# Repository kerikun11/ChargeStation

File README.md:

# ChargeStation
PICで作った携帯電話の充電器

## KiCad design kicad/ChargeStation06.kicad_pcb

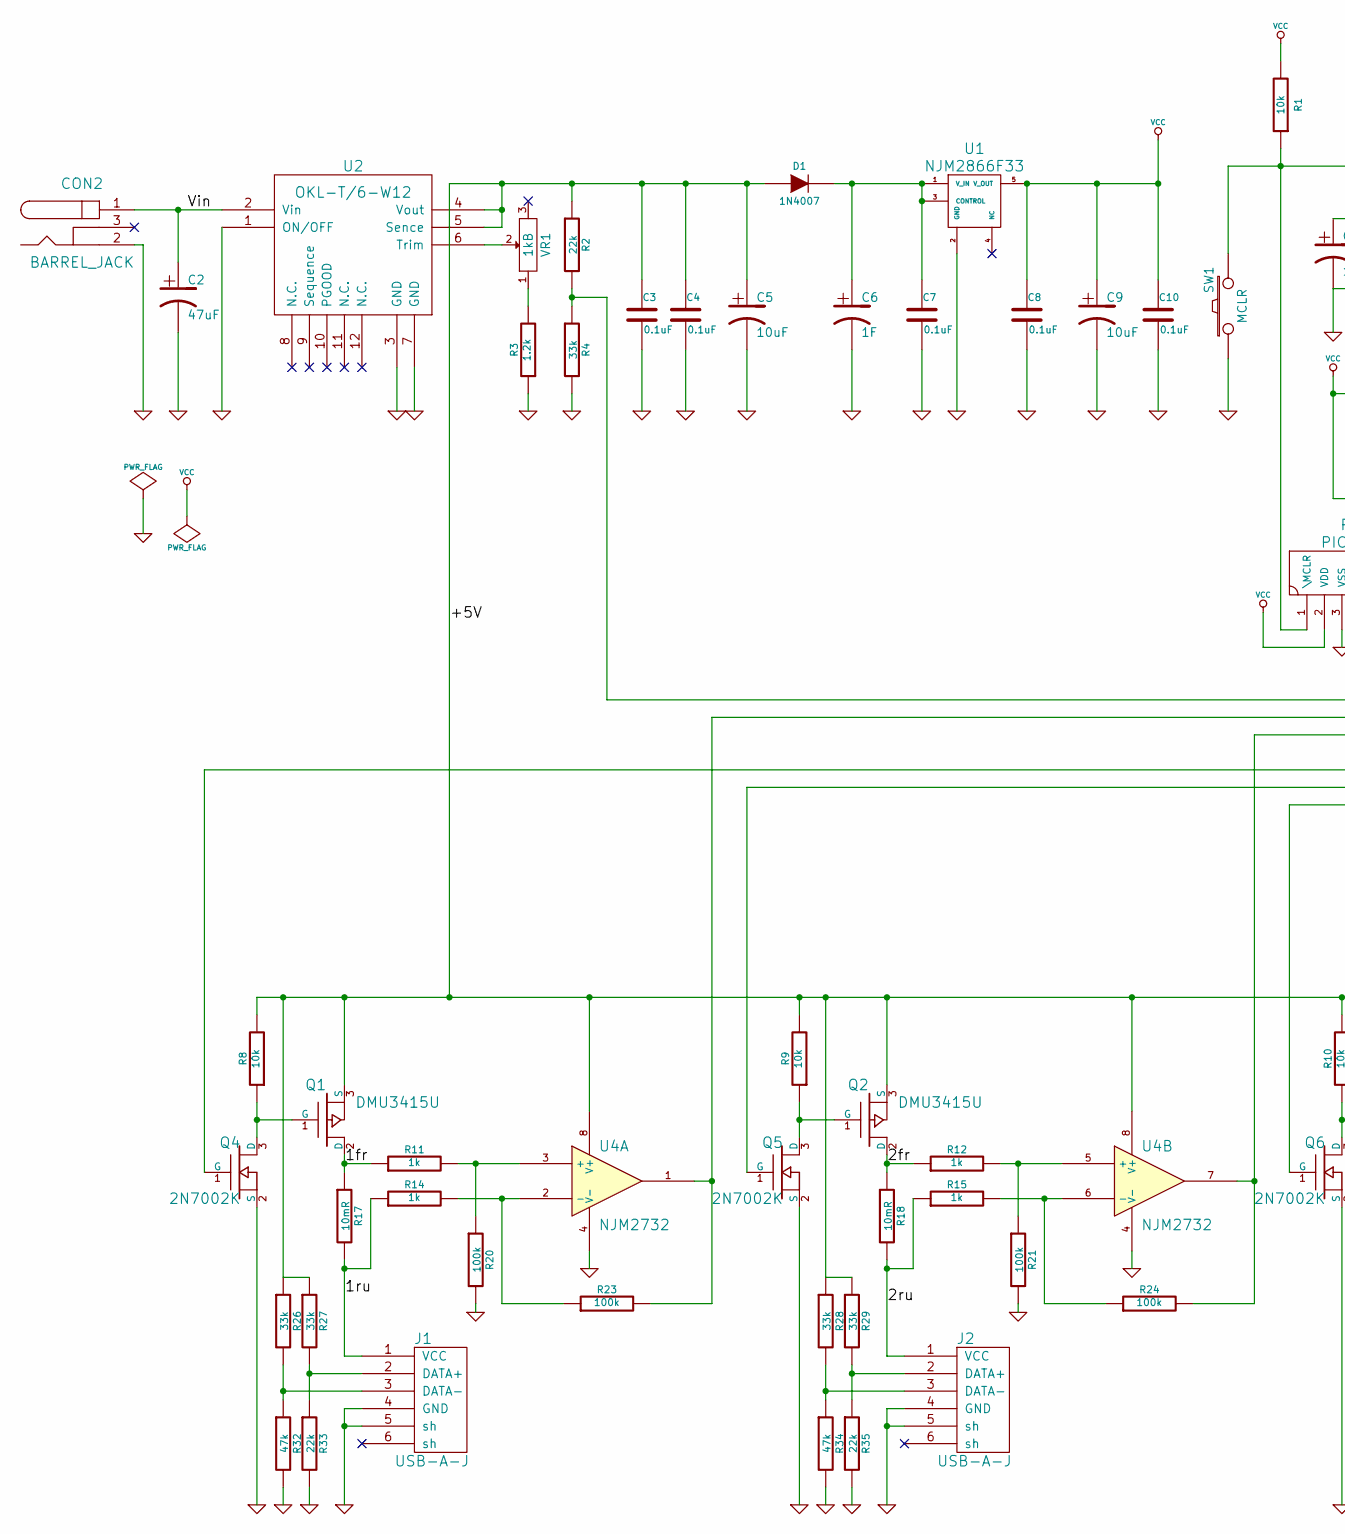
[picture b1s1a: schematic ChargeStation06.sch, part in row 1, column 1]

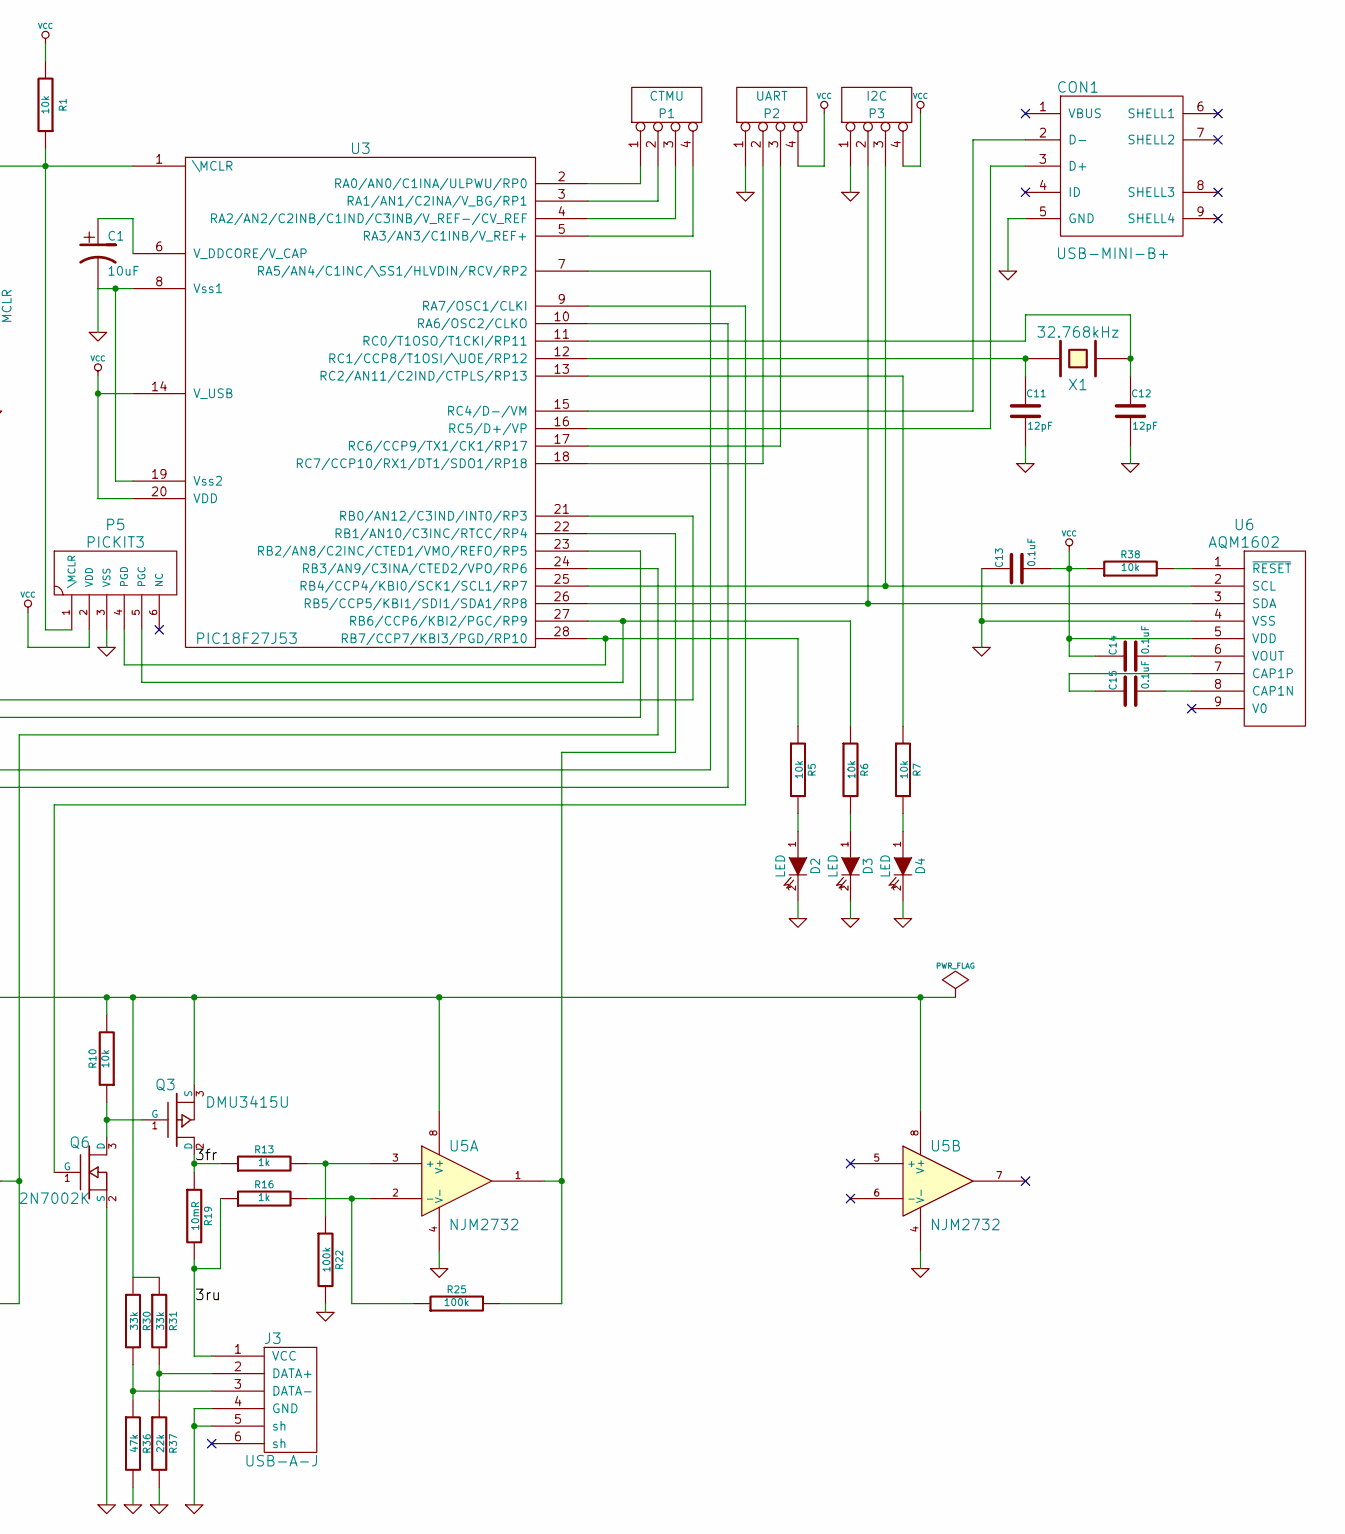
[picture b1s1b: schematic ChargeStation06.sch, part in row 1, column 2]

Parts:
C1, C5, C9: 10uF
C2: 47uF
C3, C4, C7, C8, C10, C13, C14, C15: 0.1uF
C6: 1F
C11, C12: 12pF
CON1: USB-MINI-B+
CON2: BARREL_JACK
D1: 1N4007
D2, D3, D4: LED
J1, J2, J3: USB-A-J
P1: CTMU
P2: UART
P3: I2C
P5: PICKIT3
Q1, Q2, Q3: DMU3415U
Q4, Q5, Q6: 2N7002K
R1, R5, R6, R7, R8, R9, R10, R38: 10k
R2, R33, R35, R37: 22k
R3: 1.2k
R4, R26, R27, R28, R29, R30, R31: 33k
R11, R12, R13, R14, R15, R16: 1k
R17, R18, R19: 10mR
R20, R21, R22, R23, R24, R25: 100k
R32, R34, R36: 47k
SW1: MCLR
U1: NJM2866F33
U2: OKL-T/6-W12
U3: PIC18F27J53
U4, U5: NJM2732
U6: AQM1602
VR1: 1kB
X1: 32.768kHz

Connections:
/1fr: Q1.2 (D), R11.1, R17.1
/1ru: J1.1 (VCC), R14.1, R17.2
/2fr: Q2.2 (D), R12.1, R18.1
/2ru: J2.1 (VCC), R15.1, R18.2
/3fr: Q3.2 (D), R13.1, R19.1
/3ru: J3.1 (VCC), R16.1, R19.2
/+5V: C3.1, C4.1, C5.1, D1.1 (A), Q1.3 (S), Q2.3 (S), Q3.3 (S), R2.1, R8.2, R9.2, R10.2, R26.1, R27.1, R28.1, R29.1, R30.1, R31.1, U2.4 (Vout), U2.5 (Sence), U4.8 (V+), U5.8 (V+)
/Vin: C2.1, CON2.1, U2.2 (Vin)
GND: C1.2, C2.2, C3.2, C4.2, C5.2, C6.2, C7.2, C8.2, C9.2, C10.2, C11.2, C12.2, C13.1, CON1.5 (GND), CON2.2, D2.2 (K), D3.2 (K), D4.2 (K), J1.4 (GND), J1.5 (sh), J2.4 (GND), J2.5 (sh), J3.4 (GND), J3.5 (sh), P2.1, P3.1, P5.3 (VSS), Q4.2 (S), Q5.2 (S), Q6.2 (S), R3.1, R4.2, R20.2, R21.2, R22.2, R32.2, R33.2, R34.2, R35.2, R36.2, R37.2, SW1.1, U1.2 (GND), U2.1 (ON/OFF), U2.3 (GND), U2.7 (GND), U3.8 (Vss1), U3.19 (Vss2), U4.4 (V-), U5.4 (V-), U6.4 (VSS)
unnamed: J3.3 (DATA-), R30.2, R36.1
unnamed: J3.2 (DATA+), R31.2, R37.1
unnamed: R13.2, R22.1, U5.3 (+)
unnamed: Q2.1 (G), Q5.3 (D), R9.1
unnamed: R24.2, U3.24 (RB3/AN9/C3INA/CTED2/VPO/RP6), U4.7
unnamed: R15.2, R24.1, U4.6 (-)
unnamed: Q3.1 (G), Q6.3 (D), R10.1
unnamed: R25.2, U3.22 (RB1/AN10/C3INC/RTCC/RP4), U5.1
unnamed: R16.2, R25.1, U5.2 (-)
unnamed: Q1.1 (G), Q4.3 (D), R8.1
unnamed: R23.2, U3.23 (RB2/AN8/C2INC/CTED1/VMO/REFO/RP5), U4.1
unnamed: R14.2, R23.1, U4.2 (-)
unnamed: R2.2, R4.1, U3.21 (RB0/AN12/C3IND/INT0/RP3)
unnamed: J2.3 (DATA-), R28.2, R34.1
unnamed: J2.2 (DATA+), R29.2, R35.1
unnamed: R12.2, R21.1, U4.5 (+)
unnamed: Q6.1 (G), U3.9 (RA7/OSC1/CLKI)
unnamed: CON1.2 (D-), U3.15 (RC4/D-/VM)
unnamed: R7.1, U3.13 (RC2/AN11/C2IND/CTPLS/RP13)
unnamed: P2.3, U3.17 (RC6/CCP9/TX1/CK1/RP17)
unnamed: P2.2, U3.18 (RC7/CCP10/RX1/DT1/SDO1/RP18)
unnamed: Q5.1 (G), U3.10 (RA6/OSC2/CLKO)
unnamed: Q4.1 (G), U3.7 (RA5/AN4/C1INC/\SS1/HLVDIN/RCV/RP2)
unnamed: P1.1, U3.2 (RA0/AN0/C1INA/ULPWU/RP0)
unnamed: P1.2, U3.3 (RA1/AN1/C2INA/V_BG/RP1)
unnamed: P1.4, U3.5 (RA3/AN3/C1INB/V_REF+)
unnamed: P5.1 (\MCLR), R1.1, SW1.2, U3.1 (\MCLR)
unnamed: P5.4 (PGD), R5.1, U3.28 (RB7/CCP7/KBI3/PGD/RP10)
unnamed: C1.1, U3.6 (V_DDCORE/V_CAP)
unnamed: C11.1, U3.12 (RC1/CCP8/T1OSI/\UOE/RP12), X1.2
unnamed: P5.5 (PGC), R6.1, U3.27 (RB6/CCP6/KBI2/PGC/RP9)
unnamed: C15.1, U6.7 (CAP1P)
unnamed: P3.3, U3.25 (RB4/CCP4/KBI0/SCK1/SCL1/RP7), U6.2 (SCL)
unnamed: P3.2, U3.26 (RB5/CCP5/KBI1/SDI1/SDA1/RP8), U6.3 (SDA)
unnamed: R38.2, U6.1 (~RESET)
unnamed: C14.2, U6.6 (VOUT)
unnamed: C15.2, U6.8 (CAP1N)
unnamed: J1.2 (DATA+), R27.2, R33.1
unnamed: J1.3 (DATA-), R26.2, R32.1
unnamed: R11.2, R20.1, U4.3 (+)
unnamed: P1.3, U3.4 (RA2/AN2/C2INB/C1IND/C3INB/V_REF-/CV_REF)
unnamed: D3.1 (A), R6.2
unnamed: CON1.3 (D+), U3.16 (RC5/D+/VP)
unnamed: U2.6 (Trim), VR1.2
unnamed: D2.1 (A), R5.2
unnamed: D4.1 (A), R7.2
unnamed: R3.2, VR1.1
unnamed: C6.1, C7.1, D1.2 (K), U1.1 (V_IN), U1.3 (CONTROL)
unnamed: C12.1, U3.11 (RC0/T1OSO/T1CKI/RP11), X1.1
VCC: C8.1, C9.1, C10.1, C13.2, C14.1, P2.4, P3.4, P5.2 (VDD), R1.2, R38.1, U1.5 (V_OUT), U3.14 (V_USB), U3.20 (VDD), U6.5 (VDD)

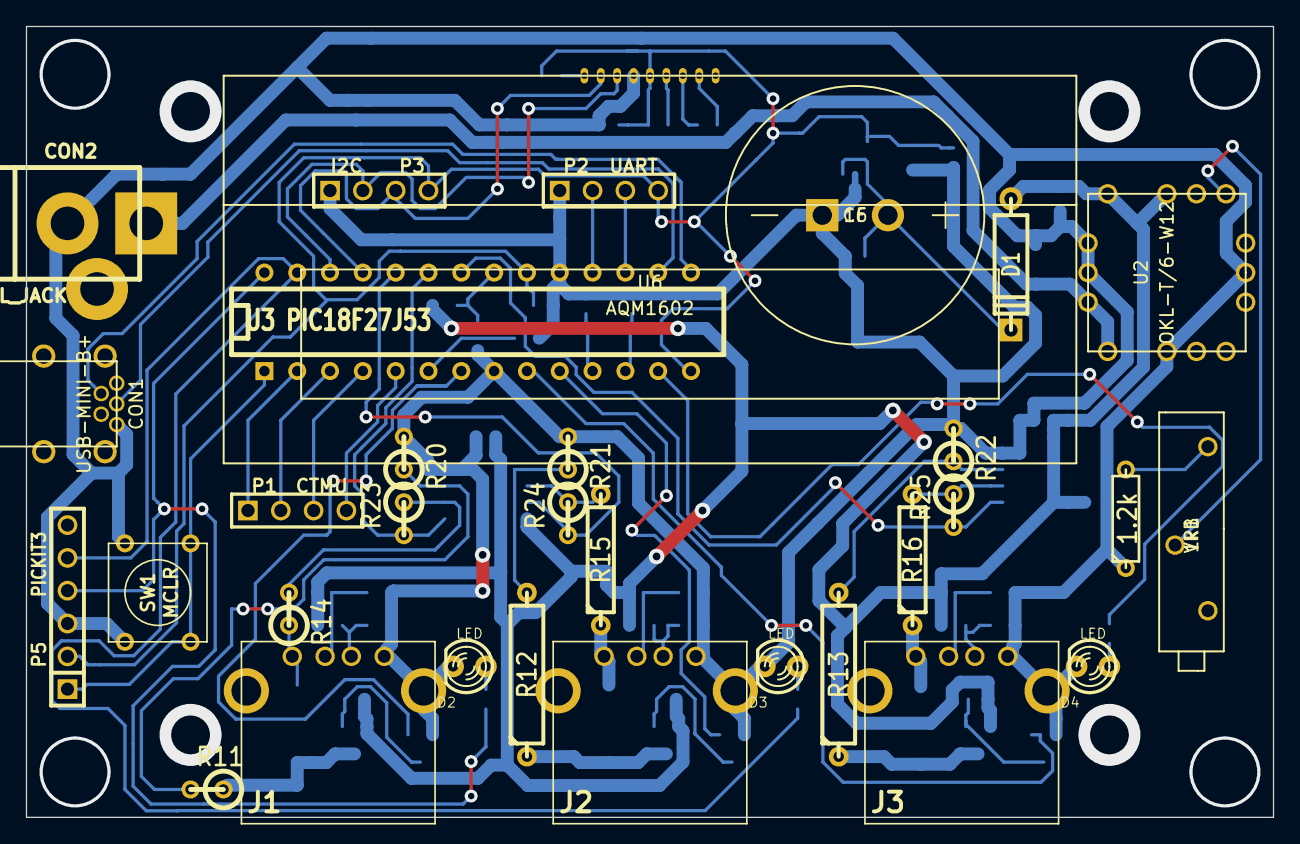
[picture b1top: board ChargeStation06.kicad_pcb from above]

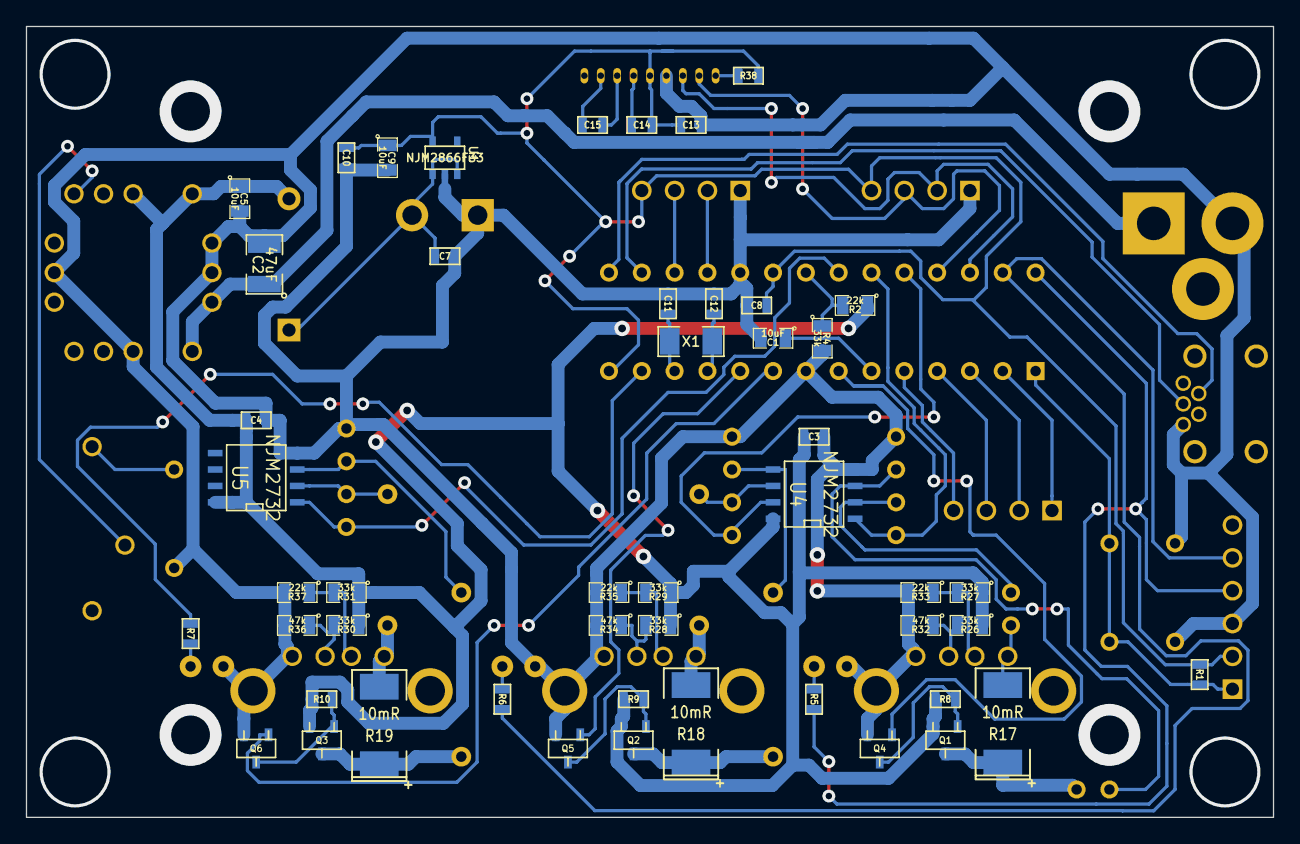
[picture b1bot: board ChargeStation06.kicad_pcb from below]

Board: 2 copper layers, 96.5 x 61.2 mm, 81 parts (49 on the bottom side), 59 nets.

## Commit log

2019-02-26 最新版を追加
